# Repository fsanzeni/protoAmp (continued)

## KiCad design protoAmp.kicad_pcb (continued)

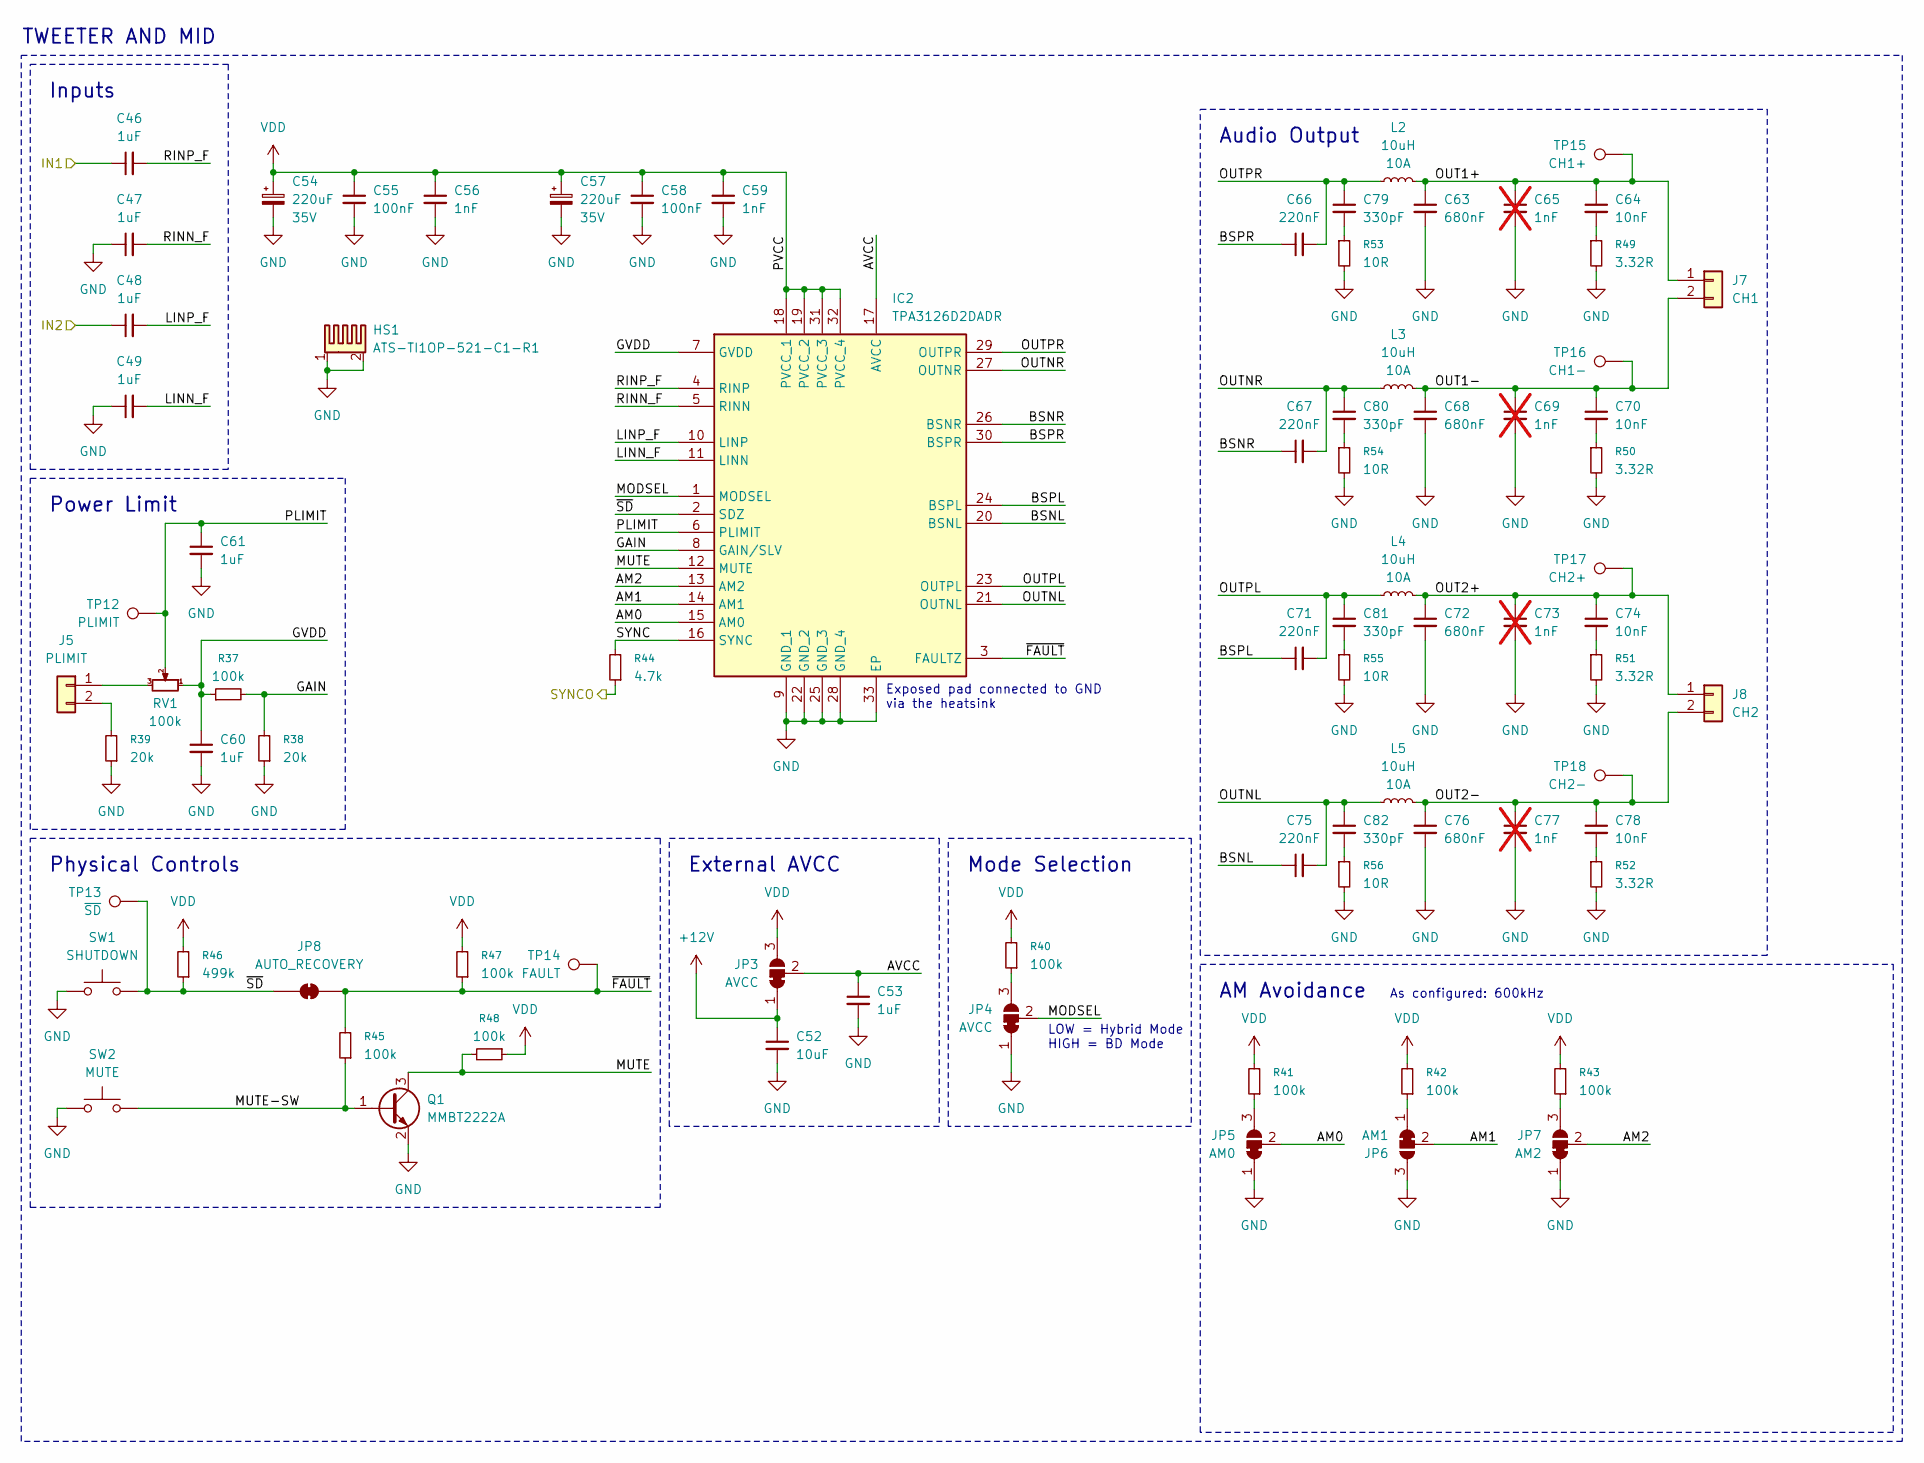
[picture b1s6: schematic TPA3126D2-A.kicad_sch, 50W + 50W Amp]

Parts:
C46, C47, C48, C49, C53: 1uF; C_0603_1608Metric
C52: 10uF; C_1210_3225Metric
C54, C57: 220uF; CP_Radial_D10.0mm_P5.00mm; Rating 35V
C55, C58: 100nF; C_0603_1608Metric
C56, C59: 1nF; C_0603_1608Metric
C60, C61: 1uF; C_0805_2012Metric
C63, C68, C72, C76: 680nF; C_1206_3216Metric
C64, C70, C74, C78: 10nF; C_0603_1608Metric
C65, C69, C73, C77: 1nF; C_0603_1608Metric; not fitted
C66, C67, C71, C75: 220nF; C_0603_1608Metric
C79, C80, C81, C82: 330pF; C_0603_1608Metric
HS1: ATS-TI1OP-521-C1-R1
IC2: TPA3126D2DADR; SOP65P810X120-33N; Mouser Part Number 595-TPA3126D2DADR
J5: PLIMIT; PinHeader_1x02_P2.54mm_Vertical
J7: CH1; TerminalBlock_Xinya_XY308-2.54-2P_1x02_P2.54mm_Horizontal
J8: CH2; TerminalBlock_Xinya_XY308-2.54-2P_1x02_P2.54mm_Horizontal
JP3, JP4: AVCC; SolderJumper-3_P1.3mm_Bridged12_Pad1.0x1.5mm
JP5: AM0; SolderJumper-3_P1.3mm_Bridged12_Pad1.0x1.5mm
JP6: AM1; SolderJumper-3_P1.3mm_Bridged12_Pad1.0x1.5mm
JP7: AM2; SolderJumper-3_P1.3mm_Bridged12_Pad1.0x1.5mm
JP8: AUTO_RECOVERY; SolderJumper-2_P1.3mm_Bridged_RoundedPad1.0x1.5mm
L2, L3, L4, L5: 10uH; SRP1265A-100M; Rating 10A
Q1: MMBT2222A; SOT-23
R37: 100k; R_0805_2012Metric
R38, R39: 20k; R_0805_2012Metric
R40, R41, R42, R43, R45, R47, R48: 100k; R_0603_1608Metric
R44: 4.7k; R_0603_1608Metric
R46: 499k; R_0603_1608Metric
R49, R50, R51, R52: 3.32R; R_0603_1608Metric
R53, R54, R55, R56: 10R; R_0805_2012Metric
RV1: 100k; Potentiometer_Bourns_3386P_Vertical
SW1: SHUTDOWN; SW_PUSH_6mm
SW2: MUTE; SW_PUSH_6mm
TP12: PLIMIT; TestPoint_Pad_1.0x1.0mm
TP13: ~{SD}; TestPoint_Pad_1.0x1.0mm
TP14: FAULT; TestPoint_Pad_1.0x1.0mm
TP15: CH1+; TestPoint_Pad_1.0x1.0mm
TP16: CH1-; TestPoint_Pad_1.0x1.0mm
TP17: CH2+; TestPoint_Pad_1.0x1.0mm
TP18: CH2-; TestPoint_Pad_1.0x1.0mm

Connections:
+12V: C52.1, JP3.1 (A); also elsewhere on the board
/ADAU1701/OUT1: C46.1; also elsewhere on the board
/ADAU1701/OUT2: C48.1; also elsewhere on the board
/Sub Amp/SYNCI: R44.1; also elsewhere on the board
/Tweeter and Mid Amp/AM0: IC2.15 (AM0), JP5.2 (C)
/Tweeter and Mid Amp/AM1: IC2.14 (AM1), JP6.2 (C)
/Tweeter and Mid Amp/AM2: IC2.13 (AM2), JP7.2 (C)
/Tweeter and Mid Amp/AVCC: C53.1, IC2.17 (AVCC), JP3.2 (C)
/Tweeter and Mid Amp/BSNL: C75.1, IC2.20 (BSNL)
/Tweeter and Mid Amp/BSNR: C67.1, IC2.26 (BSNR)
/Tweeter and Mid Amp/BSPL: C71.1, IC2.24 (BSPL)
/Tweeter and Mid Amp/BSPR: C66.1, IC2.30 (BSPR)
/Tweeter and Mid Amp/GAIN: IC2.8 (GAIN/SLV), R37.2, R38.2
/Tweeter and Mid Amp/GVDD: C60.1, IC2.7 (GVDD), R37.1, RV1.1
/Tweeter and Mid Amp/LINN_F: C49.2, IC2.11 (LINN)
/Tweeter and Mid Amp/LINP_F: C48.2, IC2.10 (LINP)
/Tweeter and Mid Amp/MODSEL: IC2.1 (MODSEL), JP4.2 (C)
/Tweeter and Mid Amp/MUTE: IC2.12 (MUTE), Q1.3 (C), R48.2
/Tweeter and Mid Amp/MUTE-SW: Q1.1 (B), R45.1, SW2.2
/Tweeter and Mid Amp/OUT1+: C63.1, C64.1, C65.1, J7.1, L2.2, TP15.1 (1_1)
/Tweeter and Mid Amp/OUT1-: C68.1, C69.1, C70.1, J7.2, L3.2, TP16.1 (1_1)
/Tweeter and Mid Amp/OUT2+: C72.1, C73.1, C74.1, J8.1, L4.2, TP17.1 (1_1)
/Tweeter and Mid Amp/OUT2-: C76.1, C77.1, C78.1, J8.2, L5.2, TP18.1 (1_1)
/Tweeter and Mid Amp/OUTNL: C75.2, C82.1, IC2.21 (OUTNL), L5.1
/Tweeter and Mid Amp/OUTNR: C67.2, C80.1, IC2.27 (OUTNR), L3.1
/Tweeter and Mid Amp/OUTPL: C71.2, C81.1, IC2.23 (OUTPL), L4.1
/Tweeter and Mid Amp/OUTPR: C66.2, C79.1, IC2.29 (OUTPR), L2.1
/Tweeter and Mid Amp/PLIMIT: C61.1, IC2.6 (PLIMIT), RV1.2, TP12.1 (1_1)
/Tweeter and Mid Amp/RINN_F: C47.2, IC2.5 (RINN)
/Tweeter and Mid Amp/RINP_F: C46.2, IC2.4 (RINP)
/Tweeter and Mid Amp/SYNC: IC2.16 (SYNC), R44.2
/Tweeter and Mid Amp/~FAULT: IC2.3 (FAULTZ), JP8.2 (B), R45.2, R47.1, TP14.1 (1_1)
/Tweeter and Mid Amp/~SD: IC2.2 (SDZ), JP8.1 (A), R46.1, SW1.2, TP13.1 (1_1)
GND: C47.1, C49.1, C52.2, C53.2, C54.2, C55.2, C56.2, C57.2, C58.2, C59.2, C60.2, C61.2, C63.2, C65.2, C68.2, C69.2, C72.2, C73.2, C76.2, C77.2, HS1.1, HS1.2, IC2.9 (GND_1), IC2.22 (GND_2), IC2.25 (GND_3), IC2.28 (GND_4), IC2.33 (EP), JP4.1 (A), JP5.1 (A), JP6.3 (B), JP7.1 (A), Q1.2 (E), R38.1, R39.1, R49.2, R50.2, R51.2, R52.2, R53.2, R54.2, R55.2, R56.2, SW1.1, SW2.1; also elsewhere on the board
unnamed: C64.2, R49.1
unnamed: C70.2, R50.1
unnamed: C74.2, R51.1
unnamed: C78.2, R52.1
unnamed: C79.2, R53.1
unnamed: C80.2, R54.1
unnamed: C81.2, R55.1
unnamed: C82.2, R56.1
unnamed: J5.1, RV1.3
unnamed: J5.2, R39.2
unnamed: JP4.3 (B), R40.1
unnamed: JP5.3 (B), R41.1
unnamed: JP6.1 (A), R42.1
unnamed: JP7.3 (B), R43.1
VDD: C54.1, C55.1, C56.1, C57.1, C58.1, C59.1, IC2.18 (PVCC_1), IC2.19 (PVCC_2), IC2.31 (PVCC_3), IC2.32 (PVCC_4), JP3.3 (B), R40.2, R41.2, R42.2, R43.2, R46.2, R47.2, R48.1; also elsewhere on the board

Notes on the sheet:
Exposed pad connected to GND via the heatsink
External AVCC
Physical Controls
As configured: 600kHz
Mode Selection
Audio Output
TWEETER AND MID
Power Limit
Inputs
AM Avoidance
LOW = Hybrid Mode HIGH = BD Mode

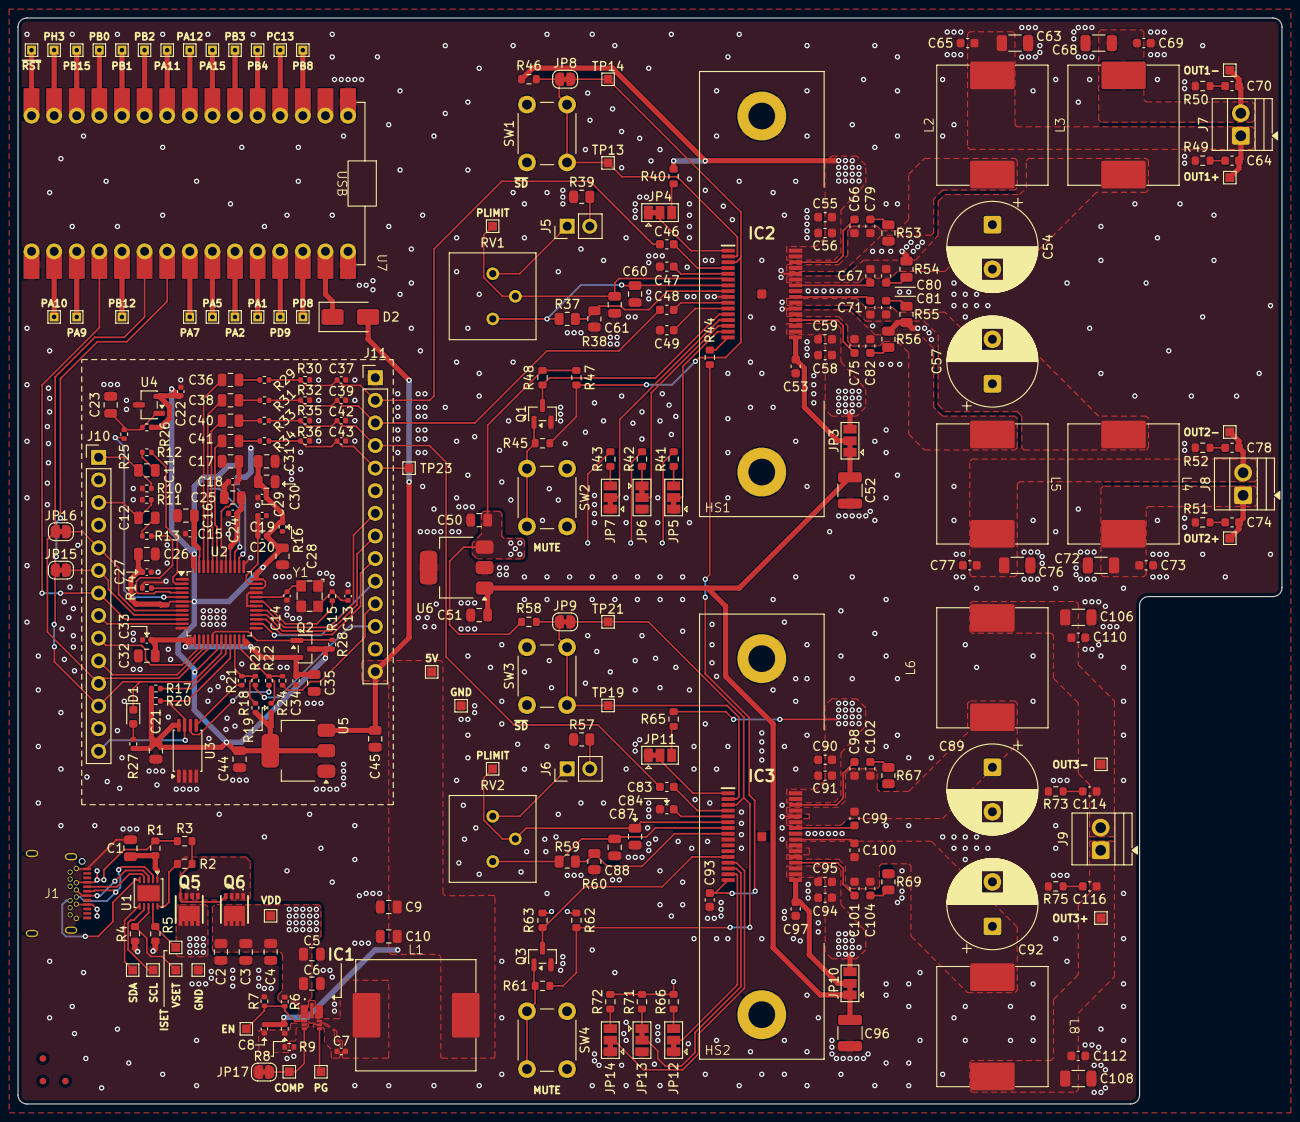
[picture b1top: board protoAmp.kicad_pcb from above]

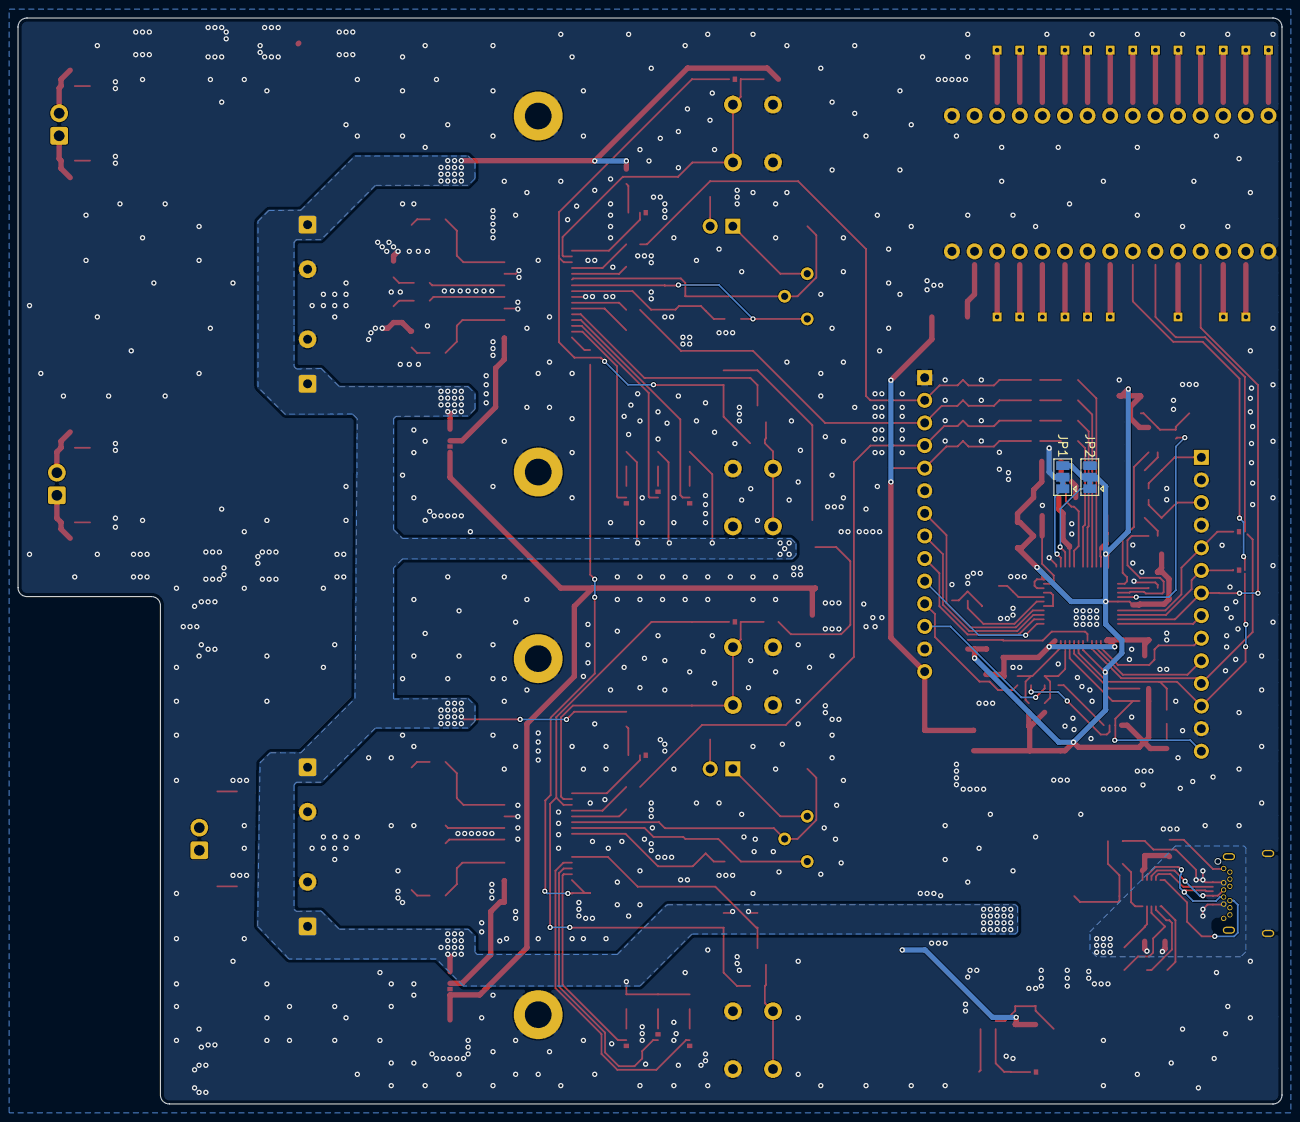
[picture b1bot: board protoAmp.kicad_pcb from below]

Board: 4 copper layers, 142.0 x 122.0 mm, 284 parts (2 on the bottom side), 177 nets.
